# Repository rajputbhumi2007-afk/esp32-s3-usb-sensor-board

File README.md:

# ESP32-S3 USB Sensor Board

A 4-layer ESP32-S3 USB sensor board designed in KiCad 10 as a PCB design learning project.

## Features
- ESP32-S3-WROOM-1 with native USB
- USB-C input with USBLC6-2SC6 ESD protection and 5.1k CC resistors
- AP2112K-3.3 LDO (5V to 3.3V)
- BME280 temperature/humidity/pressure sensor (I2C)
- Reset and BOOT buttons, user LED and power LED
- Breakout headers for IO and UART

## Design details
- 4-layer stackup: F.Cu (signals), In1.Cu (GND plane), In2.Cu (3V3 plane), B.Cu (signals)
- USB D+/D- routed as a short pair, no vias
- Net classes for power and USB
- Antenna keep-out zone
- ERC clean, DRC clean (0 errors)

## Design check
.png)

## Status
Design only. This board has not been fabricated or tested.

## Files
- `new4layer.kicad_pro`, `new4layer.kicad_sch`, `new4layer.kicad_pcb`: KiCad project
- `new4layer.pdf`: Schematic
- `new4layer-F_Cu.pdf`, `new4layer-In1_Cu.pdf`, `new4layer-In2_Cu.pdf`, `new4layer-B_Cu.pdf`, `new4layer-Edge_Cuts.pdf`, `new4layer-F_Silkscreen.pdf`: PCB layers
- `new4layer3d.png`: 3D render

## What I learned
- Why inner GND and 3V3 planes matter for return paths and noise
- Placement decides routing, so moving one part can save many tracks
- How to handle library footprint constraints while keeping a clean DRC

## Tools
KiCad 10

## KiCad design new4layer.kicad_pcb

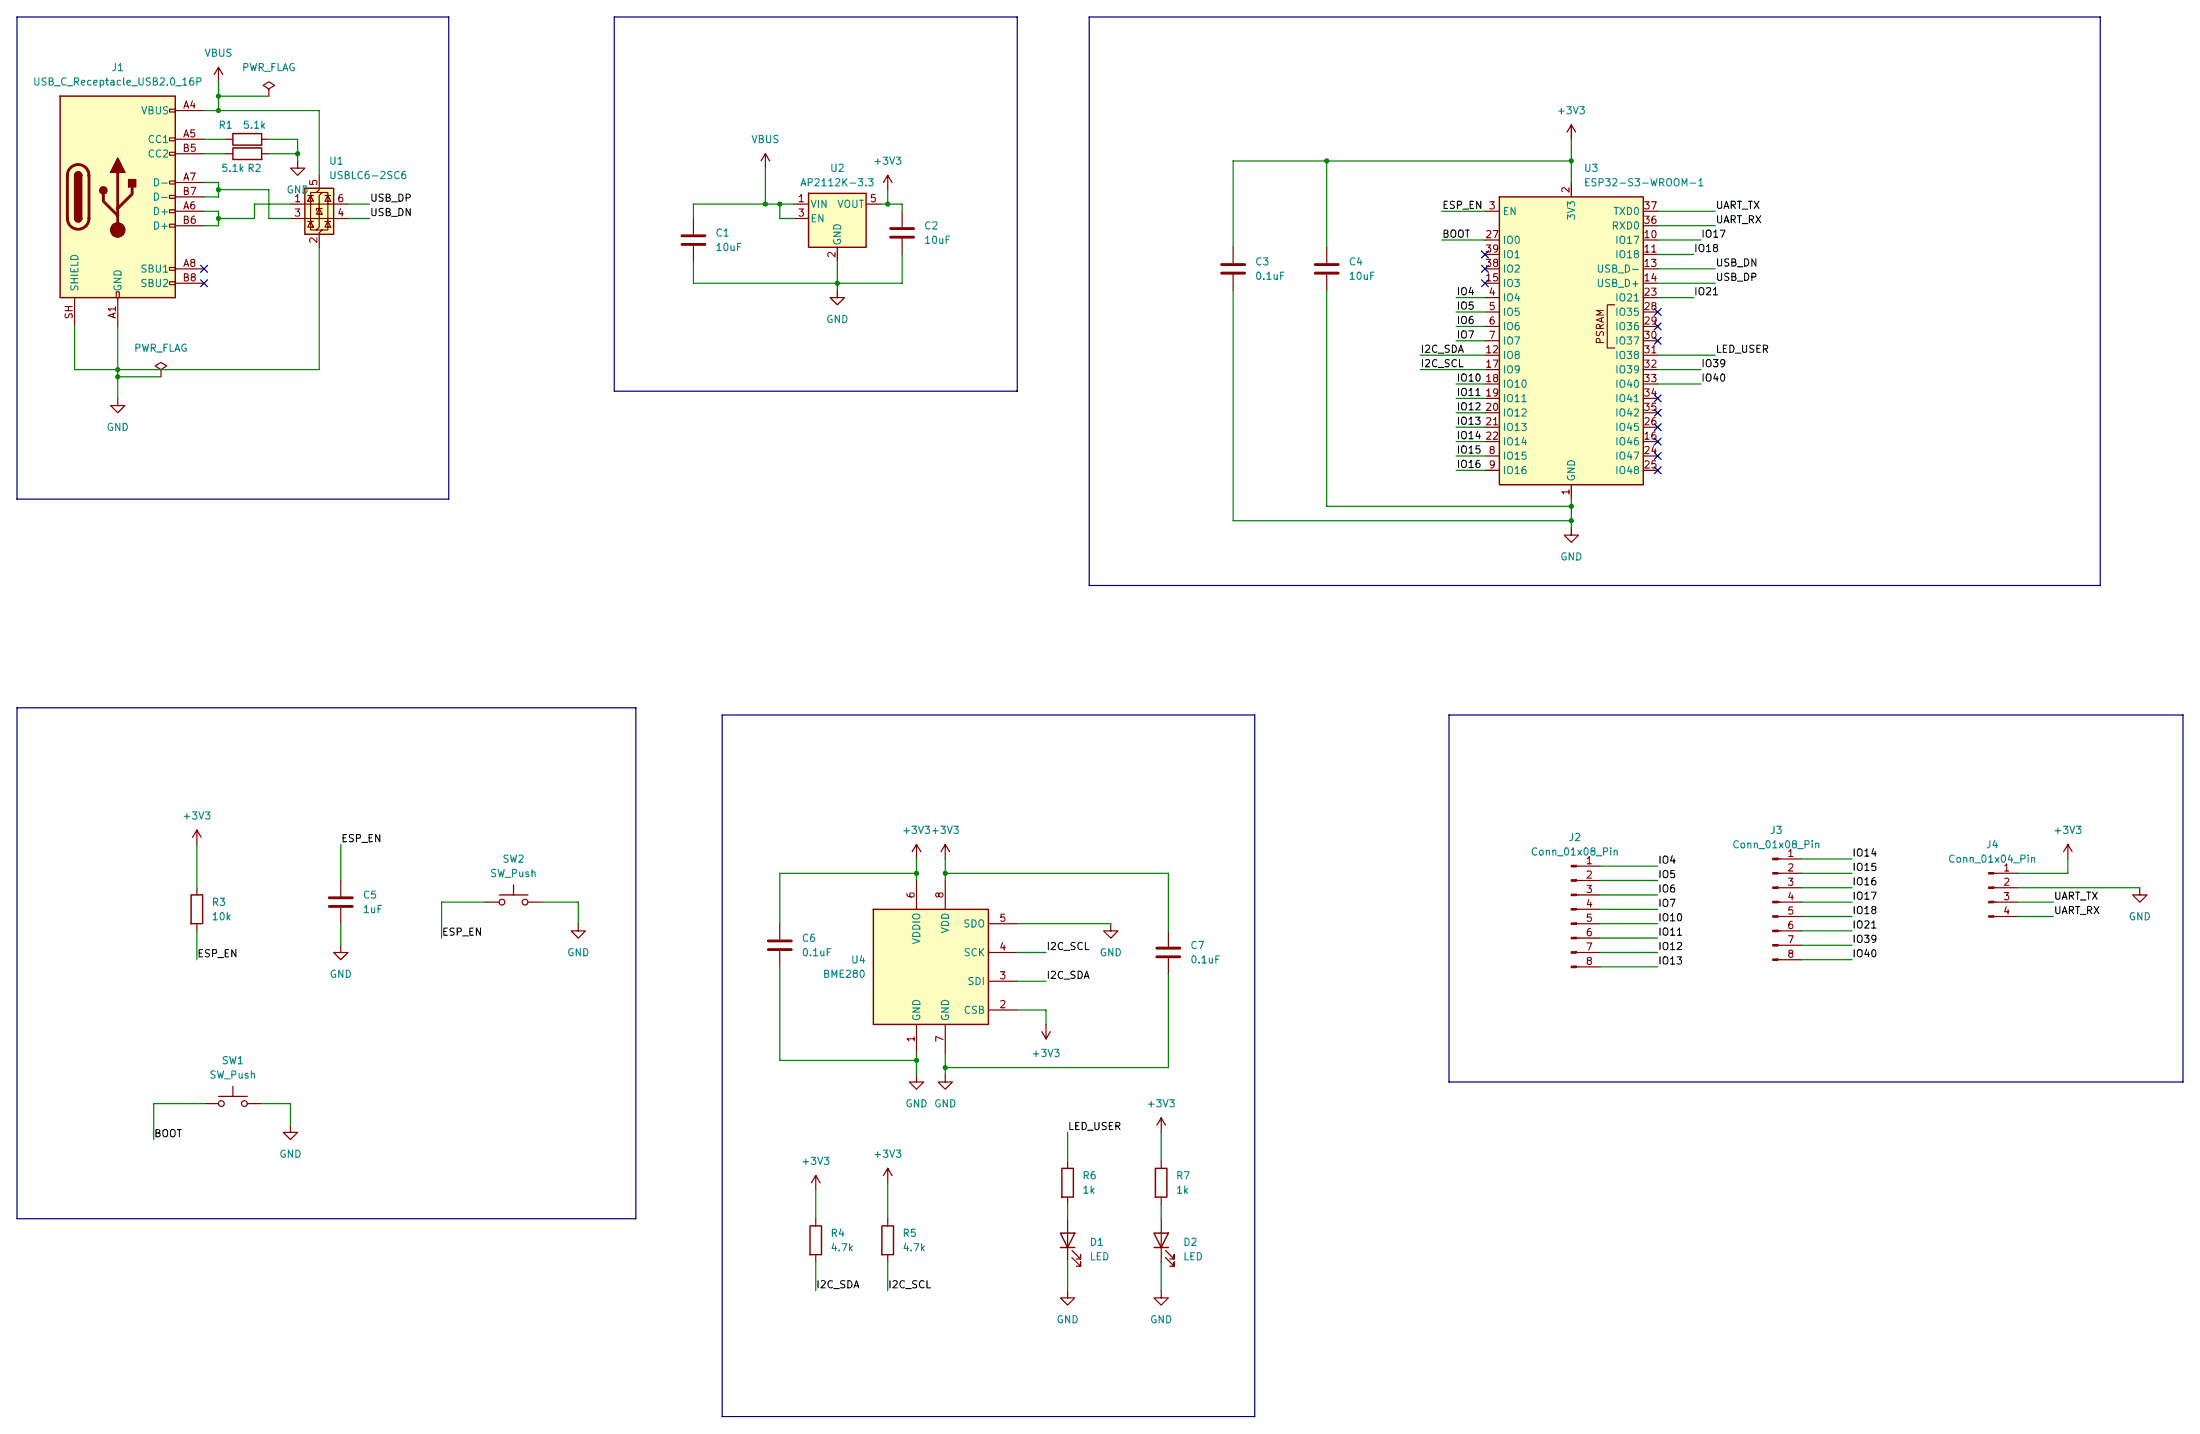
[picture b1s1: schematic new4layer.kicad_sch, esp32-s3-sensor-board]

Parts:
C1, C2, C4: 10uF; C_0603_1608Metric
C3, C6, C7: 0.1uF; C_0603_1608Metric
C5: 1uF; C_0603_1608Metric
D1, D2: LED; LED_0603_1608Metric
J1: USB_C_Receptacle_USB2.0_16P; USB_C_Receptacle_GCT_USB4105-xx-A_16P_TopMnt_Horizontal
J2, J3: Conn_01x08_Pin; PinHeader_1x08_P2.54mm_Vertical
J4: Conn_01x04_Pin; PinHeader_1x04_P2.54mm_Vertical
R1, R2: 5.1k; R_0603_1608Metric
R3: 10k; R_0603_1608Metric
R4, R5: 4.7k; R_0603_1608Metric
R6, R7: 1k; R_0603_1608Metric
SW1, SW2: SW_Push; SW_SPST_TL3342
U1: USBLC6-2SC6; SOT-23-6
U2: AP2112K-3.3; SOT-23-5
U3: ESP32-S3-WROOM-1
U4: BME280; Bosch_LGA-8_2.5x2.5mm_P0.65mm_ClockwisePinNumbering

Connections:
+3V3: C2.2, C3.1, C4.1, C6.1, C7.1, J4.1, R3.1, R4.1, R5.1, R7.1, U2.5 (VOUT), U3.2 (3V3), U4.2 (CSB), U4.6 (VDDIO), U4.8 (VDD)
/BOOT: SW1.1, U3.27 (IO0)
/ESP_EN: C5.1, R3.2, SW2.1, U3.3 (EN)
/I2C_SCL: R5.2, U3.17 (IO9), U4.4 (SCK)
/I2C_SDA: R4.2, U3.12 (IO8), U4.3 (SDI)
/IO4: J2.1, U3.4 (IO4)
/IO5: J2.2, U3.5 (IO5)
/IO6: J2.3, U3.6 (IO6)
/IO7: J2.4, U3.7 (IO7)
/IO10: J2.5, U3.18 (IO10)
/IO11: J2.6, U3.19 (IO11)
/IO12: J2.7, U3.20 (IO12)
/IO13: J2.8, U3.21 (IO13)
/IO14: J3.1, U3.22 (IO14)
/IO15: J3.2, U3.8 (IO15)
/IO16: J3.3, U3.9 (IO16)
/IO17: J3.4, U3.10 (IO17)
/IO18: J3.5, U3.11 (IO18)
/IO21: J3.6, U3.23 (IO21)
/IO39: J3.7, U3.32 (IO39)
/IO40: J3.8, U3.33 (IO40)
/LED_USER: R6.1, U3.31 (IO38)
/UART_RX: J4.4, U3.36 (RXD0)
/UART_TX: J4.3, U3.37 (TXD0)
/USB_DN: U1.4 (I/O2), U3.13 (USB_D-)
/USB_DP: U1.6 (I/O1), U3.14 (USB_D+)
GND: C1.1, C2.1, C3.2, C4.2, C5.2, C6.2, C7.2, D1.1 (K), D2.1 (K), J1.A1 (GND), J1.A12 (GND), J1.B1 (GND), J1.B12 (GND), J1.SH (SHIELD), J4.2, R1.2, R2.2, SW1.2, SW2.2, U1.2 (GND), U2.2 (GND), U3.1 (GND), U3.40 (GND), U3.41 (GND), U4.1 (GND), U4.5 (SDO), U4.7 (GND)
unnamed: D1.2 (A), R6.2
unnamed: D2.2 (A), R7.2
unnamed: J1.A5 (CC1), R1.1
unnamed: J1.B5 (CC2), R2.1
unnamed: J1.A6 (D+), J1.B6 (D+), U1.1 (I/O1)
unnamed: J1.A7 (D-), J1.B7 (D-), U1.3 (I/O2)
VBUS: C1.2, J1.A4 (VBUS), J1.A9 (VBUS), J1.B4 (VBUS), J1.B9 (VBUS), U1.5 (VBUS), U2.1 (VIN), U2.3 (EN)

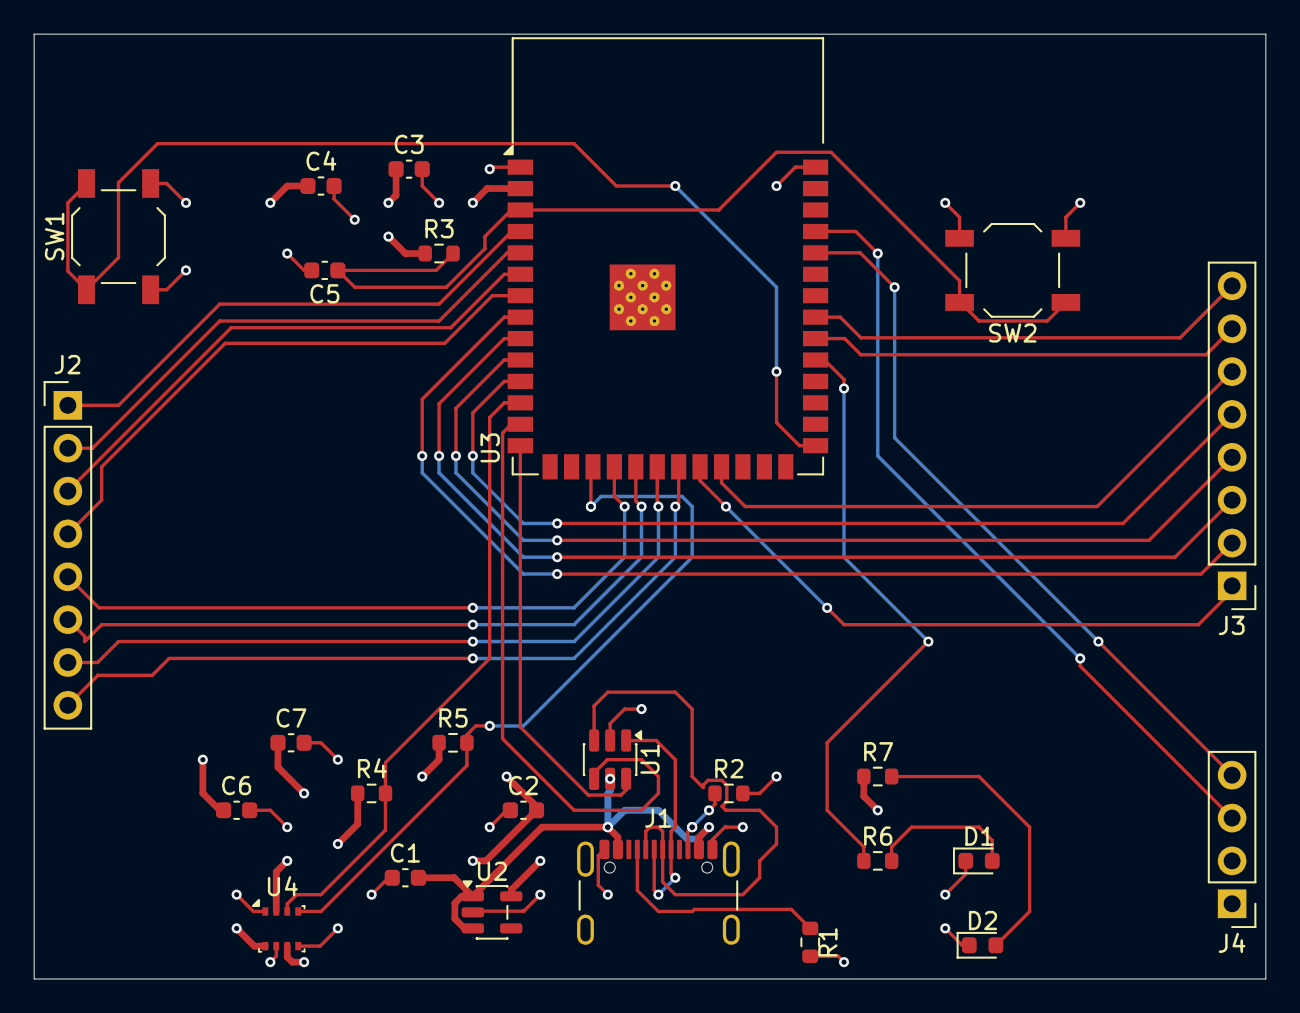
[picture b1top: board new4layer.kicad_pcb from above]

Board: 4 copper layers, 73.0 x 56.0 mm, 26 parts (0 on the bottom side), 34 nets.
